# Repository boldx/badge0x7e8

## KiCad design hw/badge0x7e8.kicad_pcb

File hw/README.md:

[KiCanvas](https://kicanvas.org/?github=https://github.com/boldx/badge0x7e8/tree/meow/hw)

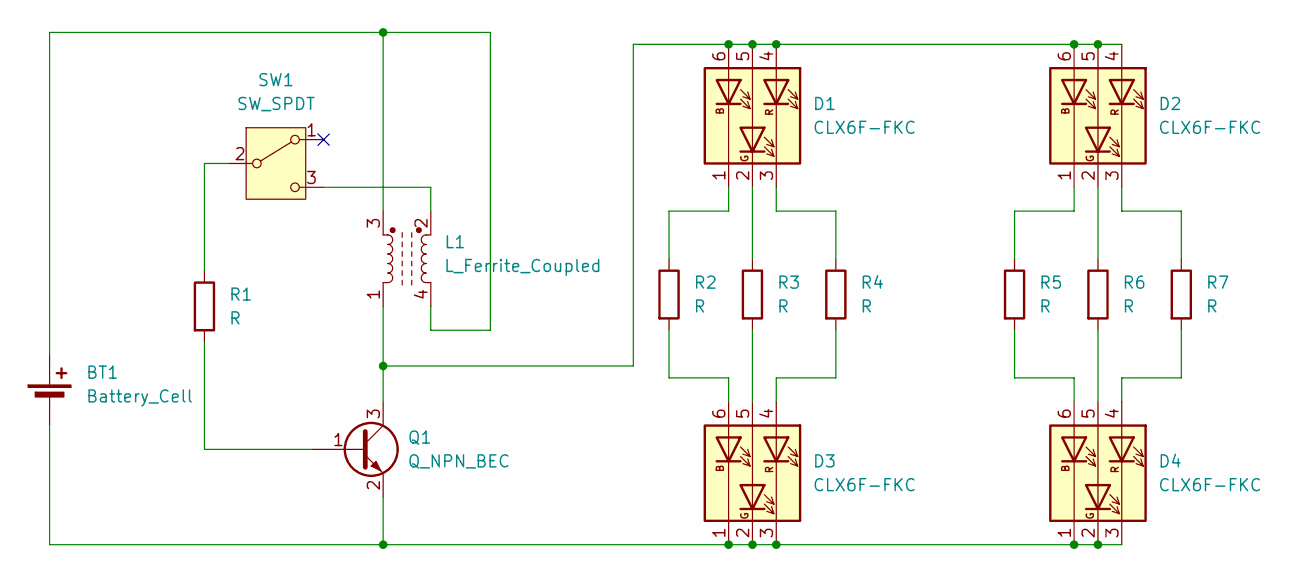
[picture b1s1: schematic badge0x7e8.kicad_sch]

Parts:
BT1: Battery_Cell; BatteryHolder_Keystone_2466_1xAAA
D1, D2, D3, D4: CLX6F-FKC; LED_RGB_Cree-PLCC-6_6x5mm_P2.1mm
L1: L_Ferrite_Coupled; L_CommonModeChoke_TDK_ACM7060
Q1: Q_NPN_BEC; SOT-23
R1, R2, R3, R4, R5, R6, R7: R; R_0805_2012Metric_Pad1.20x1.40mm_HandSolder
SW1: SW_SPDT; SW_SPDT_PCM12

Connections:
unnamed: BT1.1 (+), L1.3, L1.4
unnamed: BT1.2 (-), D3.1 (KB), D3.2 (KG), D3.3 (KR), D4.1 (KB), D4.2 (KG), D4.3 (KR), Q1.2 (E)
unnamed: D1.4 (AR), D1.5 (AG), D1.6 (AB), D2.4 (AR), D2.5 (AG), D2.6 (AB), L1.1, Q1.3 (C)
unnamed: D1.1 (KB), R2.1
unnamed: D1.2 (KG), R3.1
unnamed: D1.3 (KR), R4.1
unnamed: D2.1 (KB), R5.1
unnamed: D2.2 (KG), R6.1
unnamed: D2.3 (KR), R7.1
unnamed: D3.6 (AB), R2.2
unnamed: D3.5 (AG), R3.2
unnamed: D3.4 (AR), R4.2
unnamed: D4.6 (AB), R5.2
unnamed: D4.5 (AG), R6.2
unnamed: D4.4 (AR), R7.2
unnamed: Q1.1 (B), R1.2
unnamed: R1.1, SW1.2 (B)
unnamed: L1.2, SW1.3 (C)

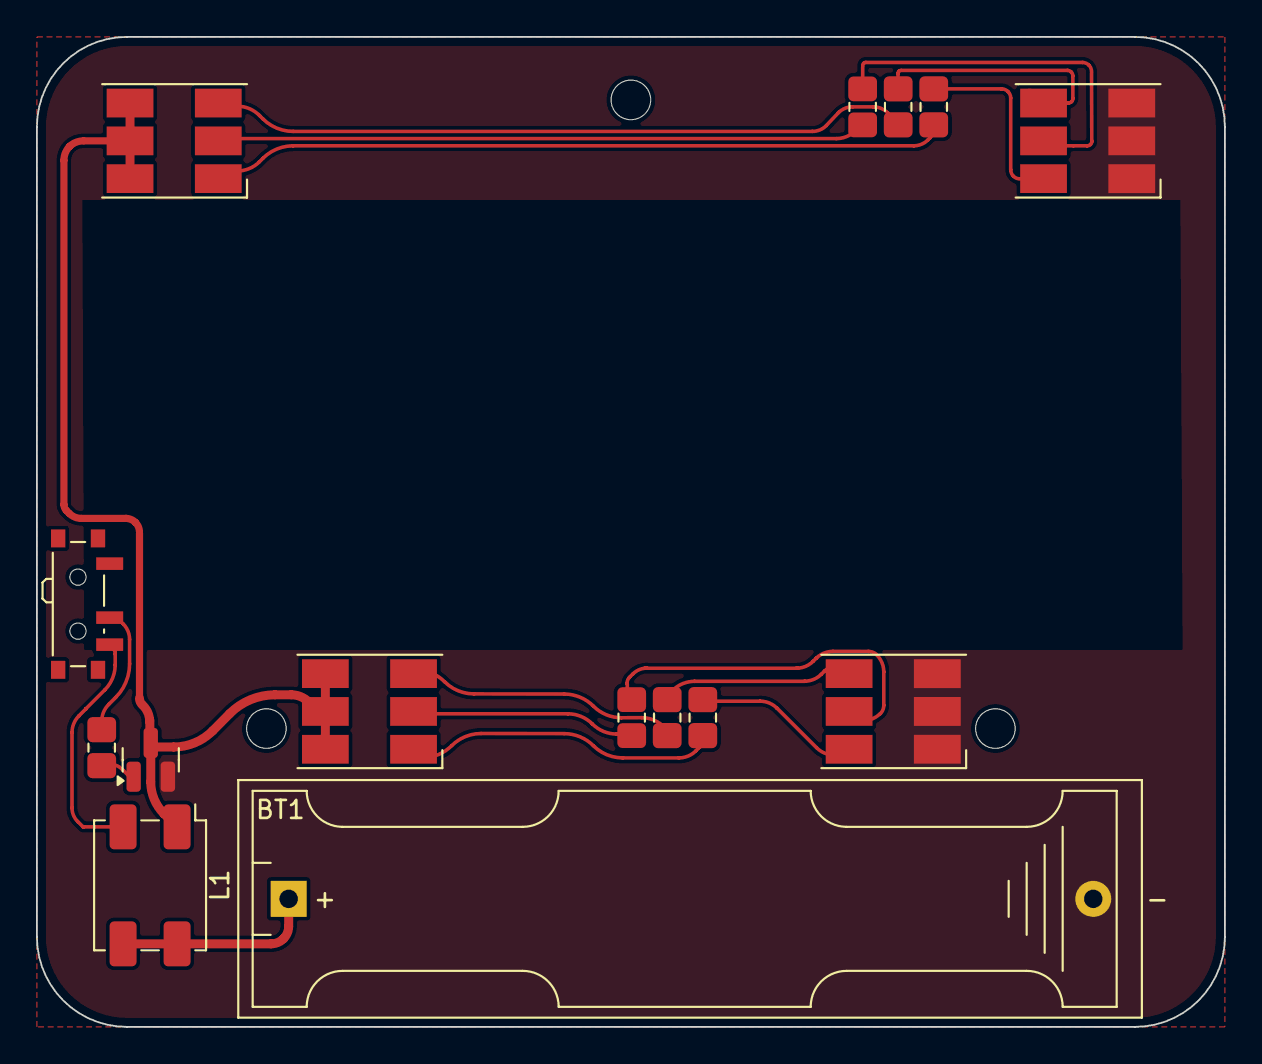
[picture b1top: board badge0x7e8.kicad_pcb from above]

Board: 2 copper layers, 66.0 x 55.0 mm, 15 parts (0 on the bottom side), 18 nets.

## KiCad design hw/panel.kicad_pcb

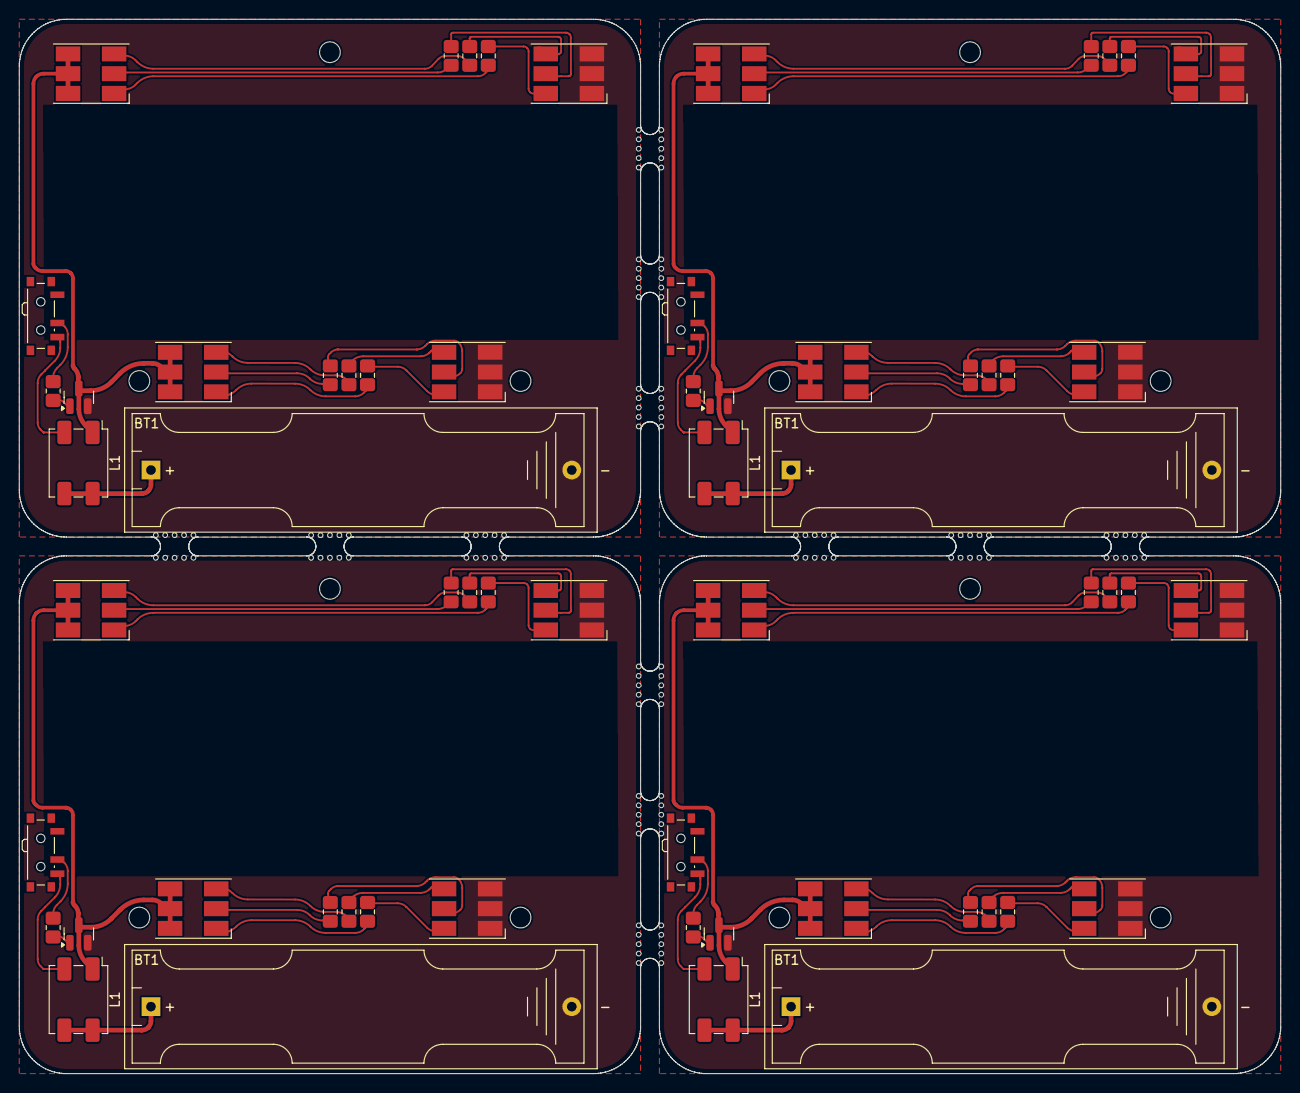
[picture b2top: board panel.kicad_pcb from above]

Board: 2 copper layers, 134.0 x 112.0 mm, 180 parts (0 on the bottom side), 72 nets.

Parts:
BT1, BT1#2, BT1#3, BT1#4: Battery_Cell; BatteryHolder_Keystone_2466_1xAAA
D1, D1#2, D1#3, D1#4, D2, D2#2, D2#3, D2#4, D3, D3#2, D3#3, D3#4, D4, D4#2, D4#3, D4#4: CLX6F-FKC; LED_RGB_Cree-PLCC-6_6x5mm_P2.1mm
KiKit_MB_1_1, KiKit_MB_1_2, KiKit_MB_1_3, KiKit_MB_1_4, KiKit_MB_1_5, KiKit_MB_2_1, KiKit_MB_2_2, KiKit_MB_2_3, KiKit_MB_2_4, KiKit_MB_2_5, KiKit_MB_3_1, KiKit_MB_3_2, KiKit_MB_3_3, KiKit_MB_3_4, KiKit_MB_3_5, KiKit_MB_4_1, KiKit_MB_4_2, KiKit_MB_4_3, KiKit_MB_4_4, KiKit_MB_4_5, KiKit_MB_5_1, KiKit_MB_5_2, KiKit_MB_5_3, KiKit_MB_5_4, KiKit_MB_5_5, KiKit_MB_6_1, KiKit_MB_6_2, KiKit_MB_6_3, KiKit_MB_6_4, KiKit_MB_6_5, KiKit_MB_7_1, KiKit_MB_7_2, KiKit_MB_7_3, KiKit_MB_7_4, KiKit_MB_7_5, KiKit_MB_8_1, KiKit_MB_8_2, KiKit_MB_8_3, KiKit_MB_8_4, KiKit_MB_8_5, KiKit_MB_9_1, KiKit_MB_9_2, KiKit_MB_9_3, KiKit_MB_9_4, KiKit_MB_9_5, KiKit_MB_10_1, KiKit_MB_10_2, KiKit_MB_10_3, KiKit_MB_10_4, KiKit_MB_10_5, KiKit_MB_11_1, KiKit_MB_11_2, KiKit_MB_11_3, KiKit_MB_11_4, KiKit_MB_11_5, KiKit_MB_12_1, KiKit_MB_12_2, KiKit_MB_12_3, KiKit_MB_12_4, KiKit_MB_12_5, KiKit_MB_13_1, KiKit_MB_13_2, KiKit_MB_13_3, KiKit_MB_13_4, KiKit_MB_13_5, KiKit_MB_14_1, KiKit_MB_14_2, KiKit_MB_14_3, KiKit_MB_14_4, KiKit_MB_14_5, KiKit_MB_15_1, KiKit_MB_15_2, KiKit_MB_15_3, KiKit_MB_15_4, KiKit_MB_15_5, KiKit_MB_16_1, KiKit_MB_16_2, KiKit_MB_16_3, KiKit_MB_16_4, KiKit_MB_16_5, KiKit_MB_17_1, KiKit_MB_17_2, KiKit_MB_17_3, KiKit_MB_17_4, KiKit_MB_17_5, KiKit_MB_18_1, KiKit_MB_18_2, KiKit_MB_18_3, KiKit_MB_18_4, KiKit_MB_18_5, KiKit_MB_19_1, KiKit_MB_19_2, KiKit_MB_19_3, KiKit_MB_19_4, KiKit_MB_19_5, KiKit_MB_20_1, KiKit_MB_20_2, KiKit_MB_20_3, KiKit_MB_20_4, KiKit_MB_20_5, KiKit_MB_21_1, KiKit_MB_21_2, KiKit_MB_21_3, KiKit_MB_21_4, KiKit_MB_21_5, KiKit_MB_22_1, KiKit_MB_22_2, KiKit_MB_22_3, KiKit_MB_22_4, KiKit_MB_22_5, KiKit_MB_23_1, KiKit_MB_23_2, KiKit_MB_23_3, KiKit_MB_23_4, KiKit_MB_23_5, KiKit_MB_24_1, KiKit_MB_24_2, KiKit_MB_24_3, KiKit_MB_24_4, KiKit_MB_24_5: NPTH
L1, L1#2, L1#3, L1#4: L_Ferrite_Coupled; L_CommonModeChoke_TDK_ACM7060
Q1, Q1#2, Q1#3, Q1#4: Q_NPN_BEC; SOT-23
R1, R1#2, R1#3, R1#4, R2, R2#2, R2#3, R2#4, R3, R3#2, R3#3, R3#4, R4, R4#2, R4#3, R4#4, R5, R5#2, R5#3, R5#4, R6, R6#2, R6#3, R6#4, R7, R7#2, R7#3, R7#4: R; R_0805_2012Metric_Pad1.20x1.40mm_HandSolder
SW1, SW1#2, SW1#3, SW1#4: SW_SPDT; SW_SPDT_PCM12

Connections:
Board_0-Net-(BT1-+): BT1#2.1 (+), L1#4.3, L1#4.4
Board_0-Net-(BT1--): BT1#2.2 (-), D3#2.1 (KB), D3#2.2 (KG), D3#2.3 (KR), D4#4.1 (KB), D4#4.2 (KG), D4#4.3 (KR), Q1.2 (E)
Board_0-Net-(D1-AB): D1#3.4 (AR), D1#3.5 (AG), D1#3.6 (AB), D2.4 (AR), D2.5 (AG), D2.6 (AB), L1#4.1, Q1.3 (C)
Board_0-Net-(D1-KB): D1#3.1 (KB), R2#4.1
Board_0-Net-(D1-KG): D1#3.2 (KG), R3.1
Board_0-Net-(D1-KR): D1#3.3 (KR), R4.1
Board_0-Net-(D2-KB): D2.1 (KB), R5#3.1
Board_0-Net-(D2-KG): D2.2 (KG), R6#3.1
Board_0-Net-(D2-KR): D2.3 (KR), R7#4.1
Board_0-Net-(D3-AB): D3#2.6 (AB), R2#4.2
Board_0-Net-(D3-AG): D3#2.5 (AG), R3.2
Board_0-Net-(D3-AR): D3#2.4 (AR), R4.2
Board_0-Net-(D4-AB): D4#4.6 (AB), R5#3.2
Board_0-Net-(D4-AG): D4#4.5 (AG), R6#3.2
Board_0-Net-(D4-AR): D4#4.4 (AR), R7#4.2
Board_0-Net-(Q1-B): Q1.1 (B), R1#4.2
Board_0-Net-(SW1-B): R1#4.1, SW1.2 (B)
Board_0-Net-(SW1-C): L1#4.2, SW1.3 (C)
Board_1-Net-(BT1-+): BT1#4.1 (+), L1#2.3, L1#2.4
Board_1-Net-(BT1--): BT1#4.2 (-), D3#4.1 (KB), D3#4.2 (KG), D3#4.3 (KR), D4#3.1 (KB), D4#3.2 (KG), D4#3.3 (KR), Q1#2.2 (E)
Board_1-Net-(D1-AB): D1.4 (AR), D1.5 (AG), D1.6 (AB), D2#4.4 (AR), D2#4.5 (AG), D2#4.6 (AB), L1#2.1, Q1#2.3 (C)
Board_1-Net-(D1-KB): D1.1 (KB), R2#3.1
Board_1-Net-(D1-KG): D1.2 (KG), R3#4.1
Board_1-Net-(D1-KR): D1.3 (KR), R4#3.1
Board_1-Net-(D2-KB): D2#4.1 (KB), R5#4.1
Board_1-Net-(D2-KG): D2#4.2 (KG), R6.1
Board_1-Net-(D2-KR): D2#4.3 (KR), R7#3.1
Board_1-Net-(D3-AB): D3#4.6 (AB), R2#3.2
Board_1-Net-(D3-AG): D3#4.5 (AG), R3#4.2
Board_1-Net-(D3-AR): D3#4.4 (AR), R4#3.2
Board_1-Net-(D4-AB): D4#3.6 (AB), R5#4.2
Board_1-Net-(D4-AG): D4#3.5 (AG), R6.2
Board_1-Net-(D4-AR): D4#3.4 (AR), R7#3.2
Board_1-Net-(Q1-B): Q1#2.1 (B), R1#3.2
Board_1-Net-(SW1-B): R1#3.1, SW1#2.2 (B)
Board_1-Net-(SW1-C): L1#2.2, SW1#2.3 (C)
Board_2-Net-(BT1-+): BT1#3.1 (+), L1#3.3, L1#3.4
Board_2-Net-(BT1--): BT1#3.2 (-), D3#3.1 (KB), D3#3.2 (KG), D3#3.3 (KR), D4.1 (KB), D4.2 (KG), D4.3 (KR), Q1#3.2 (E)
Board_2-Net-(D1-AB): D1#4.4 (AR), D1#4.5 (AG), D1#4.6 (AB), D2#2.4 (AR), D2#2.5 (AG), D2#2.6 (AB), L1#3.1, Q1#3.3 (C)
Board_2-Net-(D1-KB): D1#4.1 (KB), R2#2.1
Board_2-Net-(D1-KG): D1#4.2 (KG), R3#3.1
Board_2-Net-(D1-KR): D1#4.3 (KR), R4#2.1
Board_2-Net-(D2-KB): D2#2.1 (KB), R5#2.1
Board_2-Net-(D2-KG): D2#2.2 (KG), R6#2.1
Board_2-Net-(D2-KR): D2#2.3 (KR), R7#2.1
Board_2-Net-(D3-AB): D3#3.6 (AB), R2#2.2
Board_2-Net-(D3-AG): D3#3.5 (AG), R3#3.2
Board_2-Net-(D3-AR): D3#3.4 (AR), R4#2.2
Board_2-Net-(D4-AB): D4.6 (AB), R5#2.2
Board_2-Net-(D4-AG): D4.5 (AG), R6#2.2
Board_2-Net-(D4-AR): D4.4 (AR), R7#2.2
Board_2-Net-(Q1-B): Q1#3.1 (B), R1#2.2
Board_2-Net-(SW1-B): R1#2.1, SW1#3.2 (B)
Board_2-Net-(SW1-C): L1#3.2, SW1#3.3 (C)
Board_3-Net-(BT1-+): BT1.1 (+), L1.3, L1.4
Board_3-Net-(BT1--): BT1.2 (-), D3.1 (KB), D3.2 (KG), D3.3 (KR), D4#2.1 (KB), D4#2.2 (KG), D4#2.3 (KR), Q1#4.2 (E)
Board_3-Net-(D1-AB): D1#2.4 (AR), D1#2.5 (AG), D1#2.6 (AB), D2#3.4 (AR), D2#3.5 (AG), D2#3.6 (AB), L1.1, Q1#4.3 (C)
Board_3-Net-(D1-KB): D1#2.1 (KB), R2.1
Board_3-Net-(D1-KG): D1#2.2 (KG), R3#2.1
Board_3-Net-(D1-KR): D1#2.3 (KR), R4#4.1
Board_3-Net-(D2-KB): D2#3.1 (KB), R5.1
Board_3-Net-(D2-KG): D2#3.2 (KG), R6#4.1
Board_3-Net-(D2-KR): D2#3.3 (KR), R7.1
Board_3-Net-(D3-AB): D3.6 (AB), R2.2
Board_3-Net-(D3-AG): D3.5 (AG), R3#2.2
Board_3-Net-(D3-AR): D3.4 (AR), R4#4.2
Board_3-Net-(D4-AB): D4#2.6 (AB), R5.2
Board_3-Net-(D4-AG): D4#2.5 (AG), R6#4.2
Board_3-Net-(D4-AR): D4#2.4 (AR), R7.2
Board_3-Net-(Q1-B): Q1#4.1 (B), R1.2
Board_3-Net-(SW1-B): R1.1, SW1#4.2 (B)
Board_3-Net-(SW1-C): L1.2, SW1#4.3 (C)

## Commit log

2024-08-08 pdf export
2024-08-08 Case design and stuff
2024-08-08 LED colors
2024-10-12 Move stuff around
